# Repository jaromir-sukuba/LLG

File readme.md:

This is repository for project LLG - ligh level geolocator.
This geolocator uses movement of sun, sensed by single photoresistor, to estimate its own location on earth with accuracy of few dozens of kilometers. It is able to display and log the position for decades - 10 years of running/logging with display on, 30 years of runtime with display off, though only 22 years of logging memeory. Considering the battery has shelf life ~ 10 years, it's not that bad. 

/fw/ - MPLABX project expecting XC16 compiler to build. 

/hw/pcb/ - Eagle design files. Created in Eagle 6.4, 5x5cm, so it fits free version.

/hw/enclosure/ - FreeCad and stl files of enclosure I used

See https://hackaday.io/project/28550-light-level-geolocator for more.

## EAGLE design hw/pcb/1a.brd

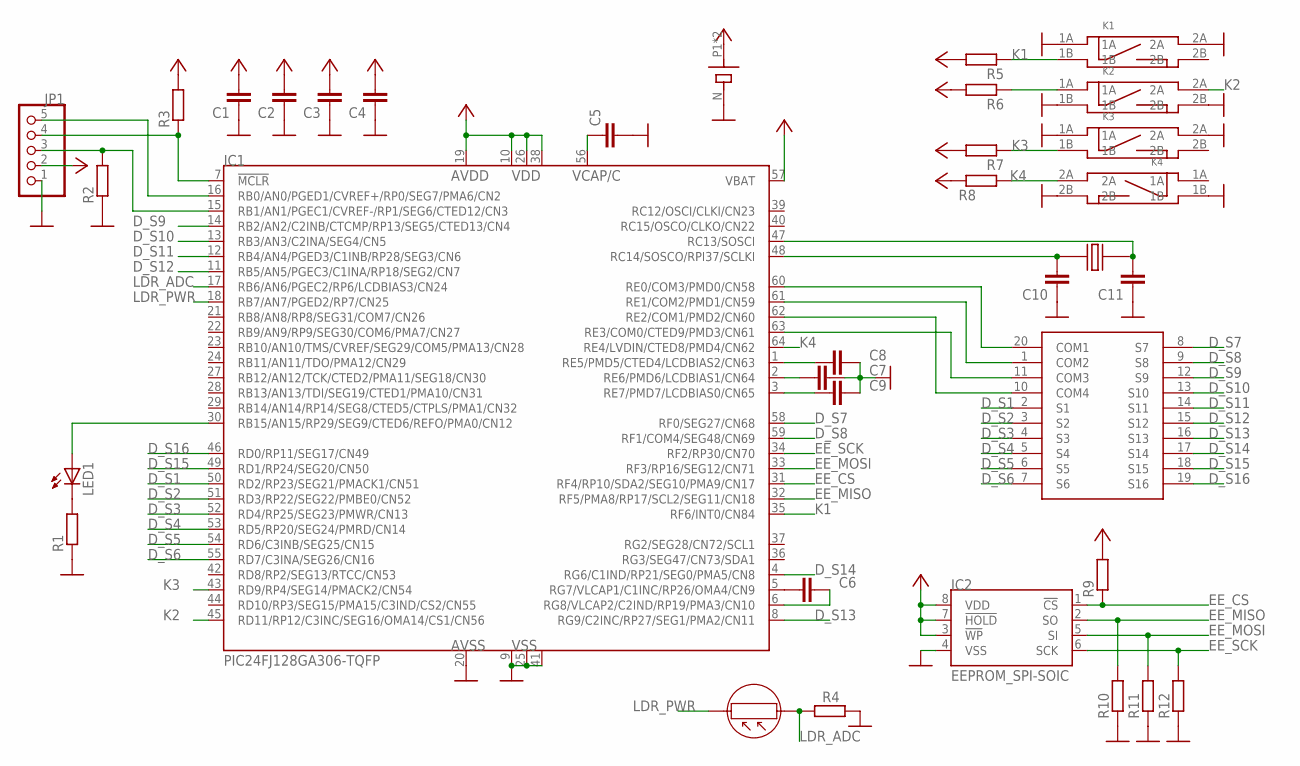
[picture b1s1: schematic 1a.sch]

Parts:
C1: C_1206; R1206
C2, C3, C4, C5, C6, C7, C8, C9, C10, C11: C_0603; 0603
IC1: PIC24FJ128GA306-TQFP; TQFP64-10X10
IC2: EEPROM_SPI-SOIC; SO-08
JP1: PINHD-1X05_2.00; 1X05M
K1, K2, K3, K4: SWITCH_BD_B; SW_SMD2
LCD1: LCD_DE188
LDR1: LDR; LDR_5
LED1: LEDCHIPLED_0805; CHIPLED_0805
R1, R2, R3, R4, R5, R6, R7, R8, R9, R10, R11, R12: R_0603; 0603
U$1: BATTK3002; BATT_KEYS3002
X1: CRYST_TC26MC146; CRYST_MC146

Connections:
D_S1: IC1.50 (RD2/RP23/SEG21/PMACK1/CN51), LCD1.2 (S1)
D_S2: IC1.51 (RD3/RP22/SEG22/PMBE0/CN52), LCD1.3 (S2)
D_S3: IC1.52 (RD4/RP25/SEG23/PMWR/CN13), LCD1.4 (S3)
D_S4: IC1.53 (RD5/RP20/SEG24/PMRD/CN14), LCD1.5 (S4)
D_S5: IC1.54 (RD6/C3INB/SEG25/CN15), LCD1.6 (S5)
D_S6: IC1.55 (RD7/C3INA/SEG26/CN16), LCD1.7 (S6)
D_S7: IC1.58 (RF0/SEG27/CN68), LCD1.8 (S7)
D_S8: IC1.59 (RF1/COM4/SEG48/CN69), LCD1.9 (S8)
D_S9: IC1.14 (RB2/AN2/C2INB/CTCMP/RP13/SEG5/CTED13/CN4), LCD1.12 (S9)
D_S10: IC1.13 (RB3/AN3/C2INA/SEG4/CN5), LCD1.13 (S10)
D_S11: IC1.12 (RB4/AN4/PGED3/C1INB/RP28/SEG3/CN6), LCD1.14 (S11)
D_S12: IC1.11 (RB5/AN5/PGEC3/C1INA/RP18/SEG2/CN7), LCD1.15 (S12)
D_S13: IC1.8 (RG9/C2INC/RP27/SEG1/PMA2/CN11), LCD1.16 (S13)
D_S14: IC1.4 (RG6/C1IND/RP21/SEG0/PMA5/CN8), LCD1.17 (S14)
D_S15: IC1.49 (RD1/RP24/SEG20/CN50), LCD1.18 (S15)
D_S16: IC1.46 (RD0/RP11/SEG17/CN49), LCD1.19 (S16)
EE_CS: IC1.31 (RF4/RP10/SDA2/SEG10/PMA9/CN17), IC2.1 (!CS), R9.1
EE_MISO: IC1.32 (RF5/PMA8/RP17/SCL2/SEG11/CN18), IC2.2 (SO), R10.2
EE_MOSI: IC1.33 (RF3/RP16/SEG12/CN71), IC2.5 (SI), R11.2
EE_SCK: IC1.34 (RF2/RP30/CN70), IC2.6 (SCK), R12.2
GND: C1.1, C2.1, C3.1, C4.1, C5.2, C7.1, C8.1, C9.1, C10.1, C11.1, IC1.9 (VSS), IC1.20 (AVSS), IC1.25 (VSS), IC1.41 (VSS), IC2.4 (VSS), JP1.1, K1.1A, K1.2A, K2.1B, K2.2B, K3.1A, K3.2A, K4.1B, K4.2B, R1.1, R2.1, R4.1, R10.1, R11.1, R12.1, U$1.N (M)
K1: IC1.35 (RF6/INT0/CN84), K1.1B, R5.1
K2: IC1.45 (RD11/RP12/C3INC/SEG16/OMA14/CS1/CN56), K2.2A
K3: IC1.43 (RD9/RP4/SEG14/PMACK2/CN54), K3.1B, R7.1
K4: IC1.64 (RE4/LVDIN/CTED8/PMD4/CN62), K4.2A, R8.2
LDR_ADC: IC1.17 (RB6/AN6/PGEC2/RP6/LCDBIAS3/CN24), LDR1.P$1, R4.2
LDR_PWR: IC1.18 (RB7/AN7/PGED2/RP7/CN25), LDR1.P$2
unnamed: C5.1, IC1.56 (C)
unnamed: C11.2, IC1.47 (RC13/SOSCI), X1.1
unnamed: C10.2, IC1.48 (RC14/SOSCO/RPI37/SCLKI), X1.4
unnamed: IC1.60 (RE0/COM3/PMD0/CN58), LCD1.20 (COM1)
unnamed: IC1.61 (RE1/COM2/PMD1/CN59), LCD1.1 (COM2)
unnamed: IC1.63 (RE3/COM0/CTED9/PMD3/CN61), LCD1.11 (COM3)
unnamed: IC1.62 (RE2/COM1/PMD2/CN60), LCD1.10 (COM4)
unnamed: C8.2, IC1.1 (RE5/PMD5/CTED4/LCDBIAS2/CN63)
unnamed: C7.2, IC1.2 (RE6/PMD6/LCDBIAS1/CN64)
unnamed: C9.2, IC1.3 (RE7/PMD7/LCDBIAS0/CN65)
unnamed: LED1.C, R1.2
unnamed: IC1.30 (RB15/AN15/RP29/SEG9/CTED6/REFO/PMA0/CN12), LED1.A
unnamed: K2.1A, R6.1
unnamed: C6.2, IC1.5 (RG7/VLCAP1/C1INC/RP26/OMA4/CN9)
unnamed: C6.1, IC1.6 (RG8/VLCAP2/C2IND/RP19/PMA3/CN10)
unnamed: IC1.15 (RB1/AN1/PGEC1/CVREF-/RP1/SEG6/CTED12/CN3), JP1.3, R2.2
unnamed: IC1.16 (RB0/AN0/PGED1/CVREF+/RP0/SEG7/PMA6/CN2), JP1.5
unnamed: IC1.7 (!MCLR), JP1.4, R3.1
VCC: C1.2, C2.2, C3.2, C4.2, IC1.10 (VDD), IC1.19 (AVDD), IC1.26 (VDD), IC1.38 (VDD), IC1.57 (VBAT), IC2.3 (!WP), IC2.7 (!HOLD), IC2.8 (VDD), JP1.2, R3.2, R5.2, R6.2, R7.2, R8.1, R9.2, U$1.P1, U$1.P2

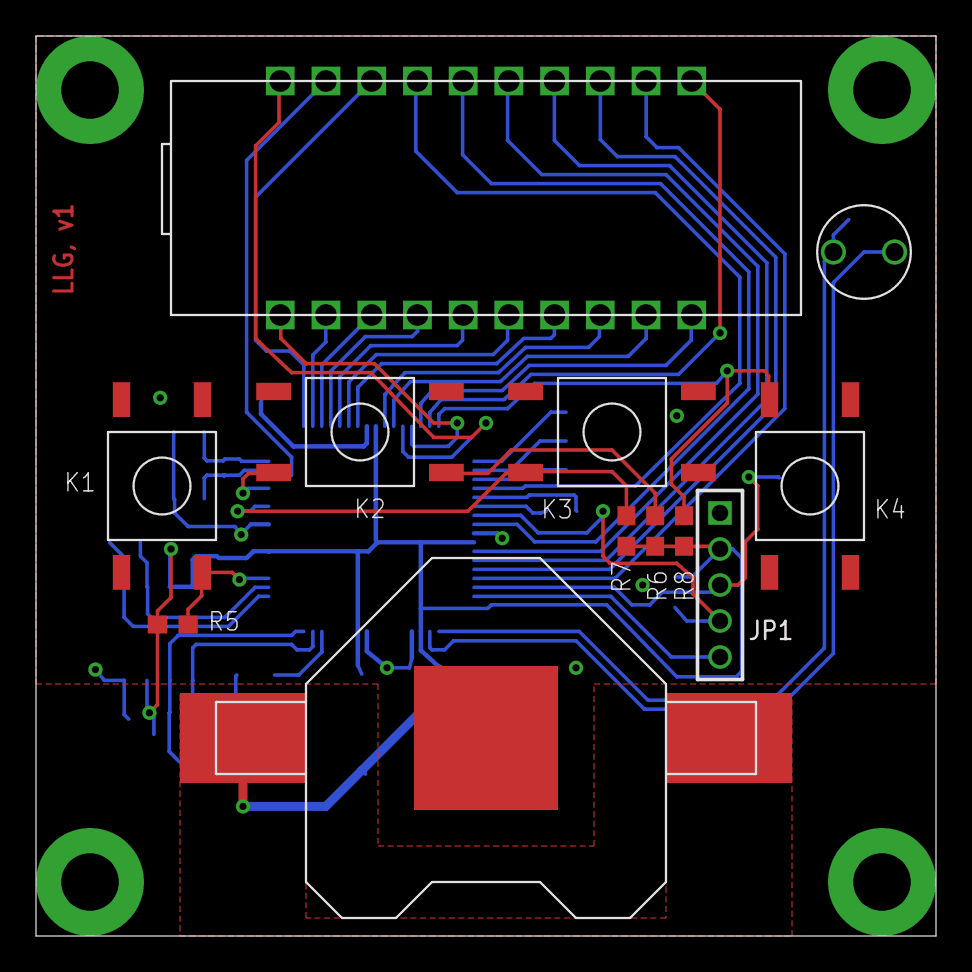
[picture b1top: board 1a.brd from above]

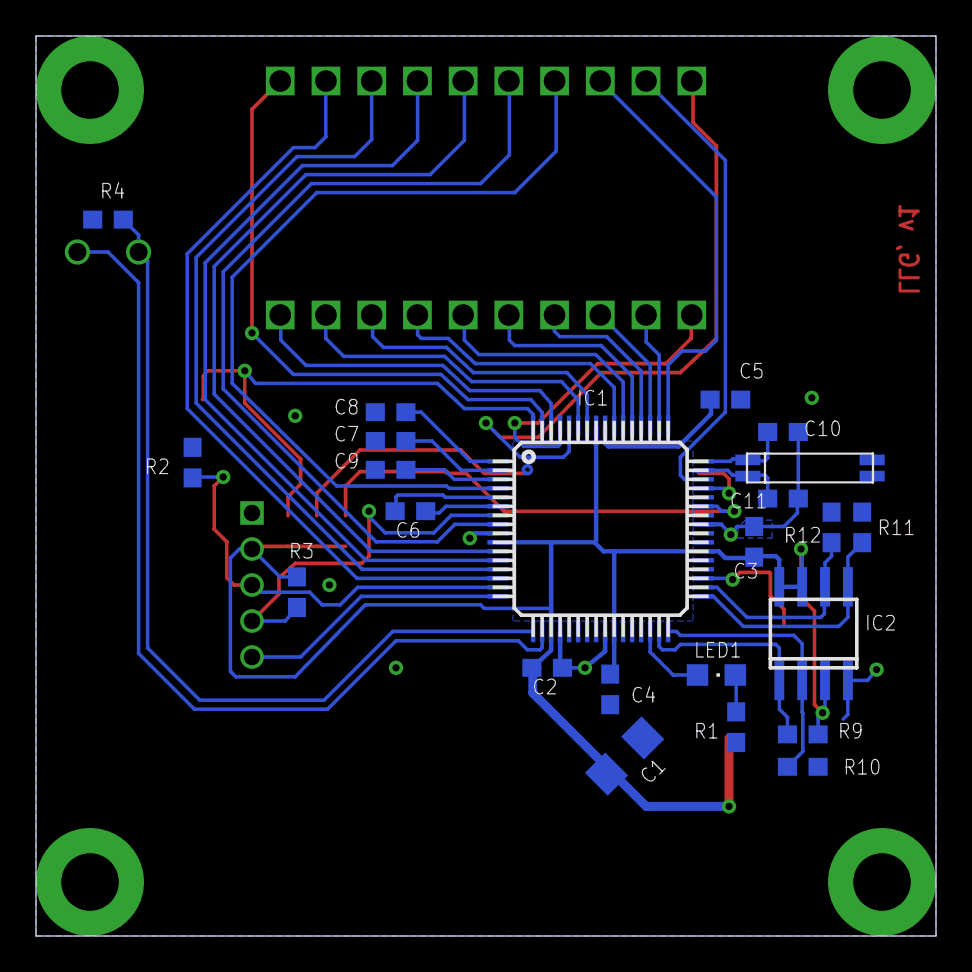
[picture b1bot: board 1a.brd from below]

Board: 2 copper layers, 50.0 x 50.0 mm, 35 parts (23 on the bottom side), 46 nets.

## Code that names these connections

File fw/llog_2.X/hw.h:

#include <xc.h>

#define		LL_LOG_SIZE	1440/1
#define     LOG_PERIOD  1   //minutes

#define     KEY_1   PORTFbits.RF6
#define     KEY_2   PORTDbits.RD11
#define     KEY_3   PORTDbits.RD9
#define     KEY_4   PORTEbits.RE4

#define     MEM_CS  LATFbits.LATF4

#define     LDR_PWR LATBbits.LATB7

#define     LDR_ADC_CHNL    6

#define     EE_SIZE        32768
#define     EE_PAGE_SIZE   4
#define     MAX_EE_LOG_PTR EE_SIZE/EE_PAGE_SIZE

#define	FCY		500000UL


typedef struct osa_msg_res_struct {
	uint8_t sec_o;
	uint8_t sec_t;
	uint8_t min_o;
	uint8_t min_t;
	uint8_t hrs_o;
	uint8_t hrs_t;
	uint8_t day_o;
	uint8_t day_t;
	uint8_t mon_o;
	uint8_t mon_t; 
} rtc_t;

typedef union
{
struct
 {
    unsigned k1:1;
    unsigned k2:1;
    unsigned k3:1;
    unsigned k4:1;
 };
unsigned char CHAR;
}key_t; 

void shdn (uint8_t lcd_state);
void enable_lcd (void);
void power_on (void);
void main_init (void);
void clock_lprc (void);
void clock_frc (void);
void rtc_read (rtc_t * rtc_val);
void rtc_write_hm (rtc_t * rtc_val);
void rtc_write_md (rtc_t * rtc_val);
uint8_t timer_elapsed (void);
uint8_t keys_state (void);

uint8_t write_spi (uint8_t data);
void ee_wren (void);
uint8_t ee_rdsr (void);
void ee_write_page (uint16_t addr, uint8_t * data, uint8_t len);
void ee_read_page (uint16_t addr, uint8_t * data, uint8_t len);

void usart_send_str (char * data);
void usart_send_str (char * data);
void write_u1 (unsigned char data);
unsigned int get_adc(uint8_t chnl);


#define MS_DISP_TIME    0
#define MS_DISP_DATE    1
#define MS_EDIT_TIME    2
#define MS_EDIT_DATE    3
#define MS_DISP_LAT     4
#define MS_DISP_LON     5
#define MS_DISP_LOG     6
#define MS_DISP_SND     7
#define MS_DISP_SENDING 8
#define MS_IDLE         9
#define MS_CALCULATE    10
#define MS_UPDATE       11
#define MS_LCDST        12

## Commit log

2018-01-07 :neckbeard: Added .gitattributes
2018-01-07 First revision
2018-01-09 update to use O3 optimization
